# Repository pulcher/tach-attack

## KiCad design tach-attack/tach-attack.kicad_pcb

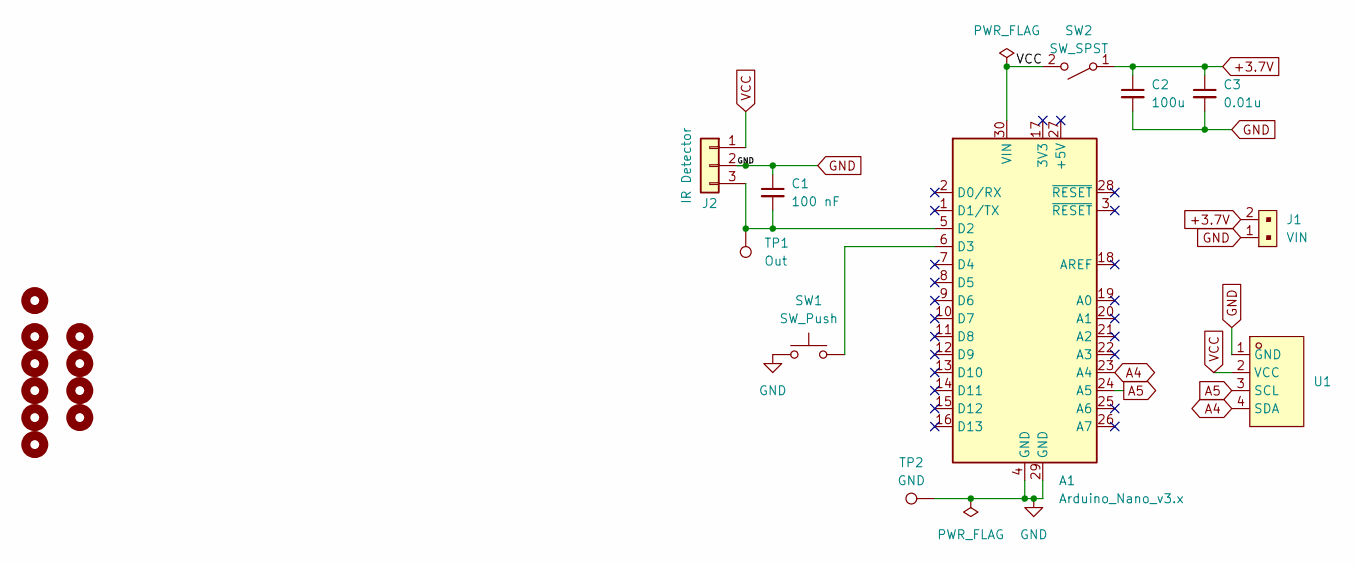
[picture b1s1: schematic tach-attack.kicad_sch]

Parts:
A1: Arduino_Nano_v3.x; Arduino_Nano
C1: 100 nF; C_Disc_D6.0mm_W2.5mm_P5.00mm
C2: 100u; C_Disc_D6.0mm_W2.5mm_P5.00mm
C3: 0.01u; C_Disc_D6.0mm_W2.5mm_P5.00mm
H1, H2, H3, H4, H5, H6, H7, H8, H9, H10: MountingHole; MountingHole_2.5mm_Pad
J1: VIN; PinHeader_1x02_P2.54mm_Vertical; MPN 22-23-2021; Digi-Key_PN WM4200-ND
J2: IR Detector; PinSocket_1x03_P2.54mm_Horizontal
SW1: SW_Push; PinHeader_1x02_P2.54mm_Vertical
SW2: SW_SPST; PinHeader_1x02_P2.54mm_Vertical
TP1: Out; TestPoint_THTPad_D1.5mm_Drill0.7mm
TP2: GND; TestPoint_THTPad_D1.5mm_Drill0.7mm
U1: HS96L03W2C03; OLED-TH_L27.8-W27.2-P2.54_C9900033791; LCSC Part C5248080

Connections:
+3.7V: C2.1, C3.1, J1.2, SW2.1 (A)
A4: A1.23 (A4), U1.4 (SDA)
A5: A1.24 (A5), U1.3 (SCL)
GND: A1.4 (GND), A1.29 (GND), C1.1, C2.2, C3.2, J1.1, J2.2, SW1.1, TP2.1, U1.1 (GND)
unnamed: A1.5 (D2), C1.2, J2.3, TP1.1
unnamed: A1.6 (D3), SW1.2
VCC: A1.30 (VIN), J2.1, SW2.2 (B), U1.2 (VCC)

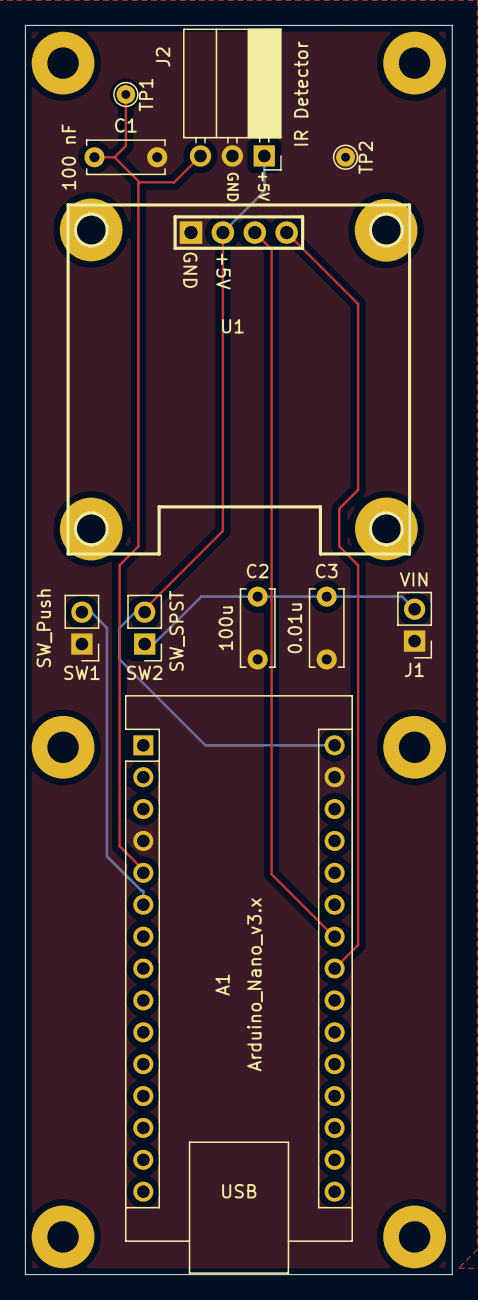
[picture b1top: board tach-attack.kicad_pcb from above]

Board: 2 copper layers, 34.0 x 99.5 mm, 21 parts (0 on the bottom side), 7 nets.

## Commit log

2024-11-05 initial
